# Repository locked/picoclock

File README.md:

# RP2040 based Alarm Clock

## Presentation

This repo is an attempt at building a Pico based alarm clock. It was created for my kids and features:

- date/time (obviously)
- alarm (plays wav file on sdcard)
- weather (current and forecast)
- epaper screen
- 3d printable case

The configuration is done remotely, and the clock synchronize from time to time (it can be forced too). The time is also fetched from a remote server.

## Repository Architecture

- **3d**: contains printable models for the case, buttons
- **fw**: the firmware, based on a lightweight "rtos"
- **pcb**: the PCBs:
  - the main PCB receiving the RP2040 board
  - the front PCB with the backlight leds
- **api**: remote api basic php script

## Pictures

## Build

```
mkdir build
cd build
cmake -DCMAKE_BUILD_TYPE=Debug ..
make
```

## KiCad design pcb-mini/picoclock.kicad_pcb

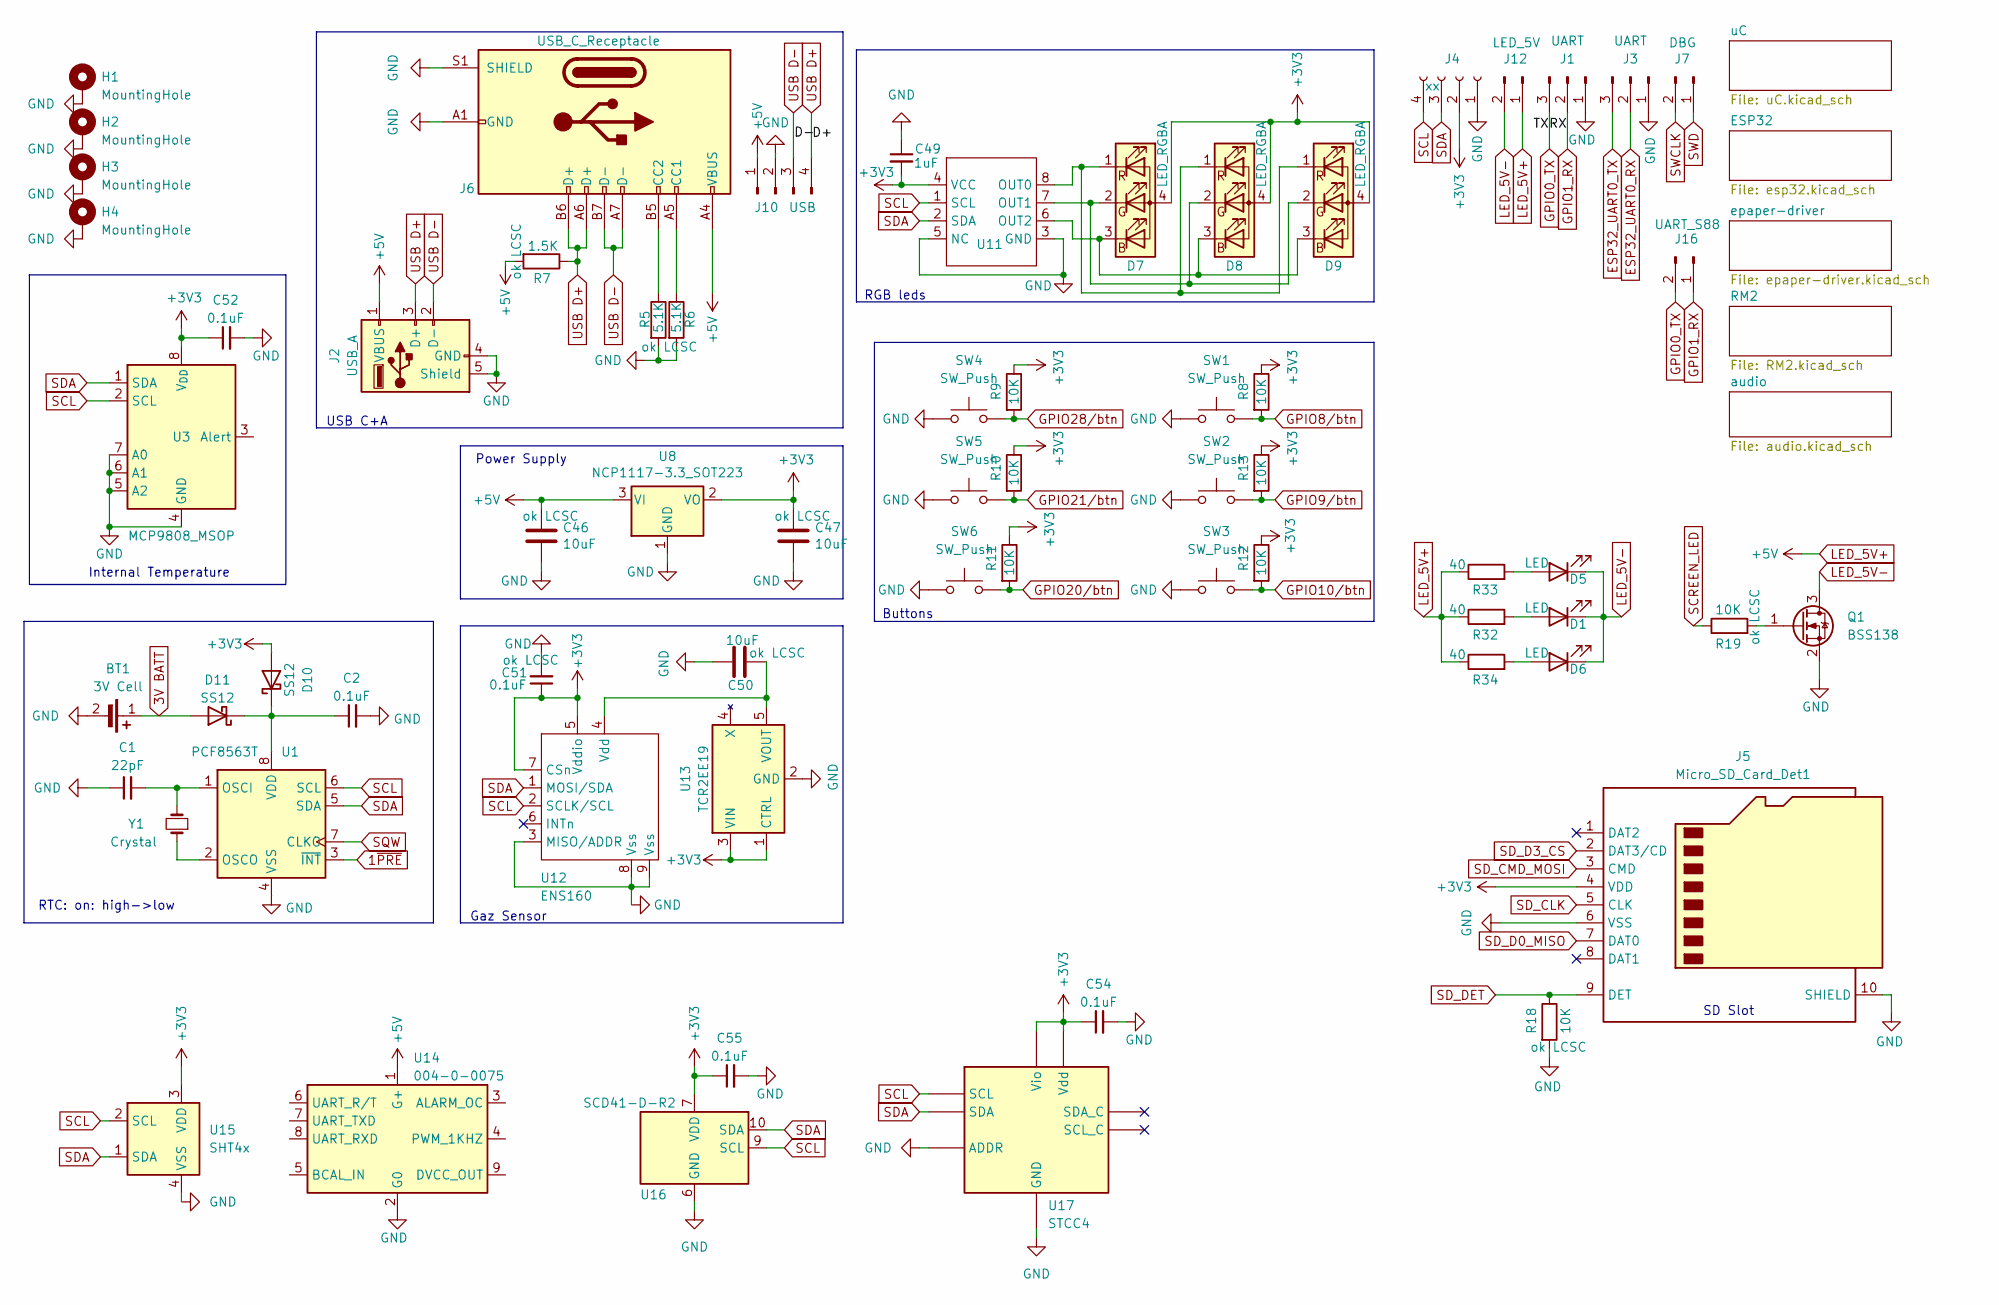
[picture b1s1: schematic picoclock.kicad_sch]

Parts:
BT1: 3V Cell; MPD_BC501SM-TR
C1: 22pF; C_0603_1608Metric; LCSC C1653
C2, C51, C52, C54, C55: 0.1uF; C_0603_1608Metric; LCSC C14663
C46, C47, C50: 10uF; C_0805_2012Metric; LCSC C15850
C49: 1uF; C_0603_1608Metric
D1, D5, D6: LED; LED_PLCC_2835
D7, D8, D9: LED_RGBA; LED_LiteOn_LTST-C19HE1WT
D10, D11: SS12; D_SOD-323
H1, H2, H3, H4: MountingHole; MountingHole_3.2mm_M3_Pad
J1, J3: UART; PinHeader_1x03_P2.54mm_Vertical
J2: USB_A; USB_A_Connfly_DS1095
J4: xx; PinSocket_1x04_P2.54mm_Vertical
J5: Micro_SD_Card_Det1; microSD_HC_Hirose_DM3AT-SF-PEJM5_combined_MSD-4-A
J6: USB_C_Receptacle; USB_C_Receptacle_GCT_USB4105-xx-A_16P_TopMnt_Horizontal
J7: DBG; PinHeader_1x02_P2.54mm_Vertical
J10: USB; PinHeader_1x04_P2.54mm_Vertical
J12: LED_5V; PinHeader_1x02_P2.54mm_Vertical
J16: UART_S88; PinHeader_1x02_P2.54mm_Vertical
Q1: BSS138; SOT-23-3
R5, R6: 5.1K; R_0603_1608Metric; LCSC C23186
R7: 1.5K; R_0603_1608Metric; LCSC C22843
R8, R9, R10, R11, R12, R13: 10K; R_0603_1608Metric; LCSC C25744
R18, R19: 10K; R_0402_1005Metric; LCSC C25744
R32, R33, R34: 40; R_0603_1608Metric
SW1, SW2, SW3, SW4, SW5, SW6: SW_Push; SW_SPST_TL3301TG
U1: PCF8563T; SOIC-8_3.9x4.9mm_P1.27mm; LCSC C7440
U3: MCP9808_MSOP; MSOP-8_3x3mm_P0.65mm; LCSC C129490
U8: NCP1117-3.3_SOT223; SOT-223-3_TabPin2
U11: LP5817
U12: ENS160
U13: TCR2EE19; SC-74A-5_1.55x2.9mm_P0.95mm
U14: 004-0-0075
U15: SHT4x; Sensirion_DFN-4_1.5x1.5mm_P0.8mm_SHT4x_NoCentralPad
U16: SCD41-D-R2; Sensirion_SCD4x-1EP_10.1x10.1mm_P1.25mm_EP4.8x4.8mm
U17: STCC4; LCSC C49191471
Y1: Crystal; Crystal_SMD_3215-2Pin_3.2x1.5mm; LCSC C32346

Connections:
1~PRE: U1.3 (~INT); also elsewhere on the board
3V BATT: BT1.1 (+), D11.2 (A)
+3V3: C47.1, C49.2, C51.1, C52.1, C54.1, C55.1, D7.4 (A), D8.4 (A), D9.4 (A), D10.2 (A), J4.2, J5.4 (VDD), R8.1, R9.1, R10.1, R11.1, R12.1, R13.1, U3.8 (V_{DD}), U8.2 (VO), U11.4 (VCC), U12.5 (Vddio), U12.7 (CSn), U13.1 (CTRL), U13.3 (VIN), U15.3 (VDD), U16.7 (VDD), U16.19 (VDD), U17.6 (Vio), U17.7 (Vdd); also elsewhere on the board
ESP32_UART0_RX: J3.2; also elsewhere on the board
ESP32_UART0_TX: J3.3; also elsewhere on the board
GND: BT1.2 (-), C1.1, C2.2, C46.2, C47.2, C49.1, C50.2, C51.2, C52.2, C54.2, C55.2, H1.1, H2.1, H3.1, H4.1, J1.1, J2.4 (GND), J2.5 (Shield), J3.1, J4.1, J5.6 (VSS), J5.10 (SHIELD), J6.A1 (GND), J6.A12 (GND), J6.B1 (GND), J6.B12 (GND), J6.S1 (SHIELD), J10.2, Q1.2 (S), R5.2, R6.2, R18.2, SW1.1, SW2.1, SW3.1, SW4.1, SW5.1, SW6.1, U1.4 (VSS), U3.4 (GND), U3.5 (A2), U3.6 (A1), U3.7 (A0), U8.1 (GND), U11.3 (GND), U11.5 (NC), U12.3 (MISO/ADDR), U12.8 (Vss), U12.9 (Vss), U13.2 (GND), U14.2 (G0), U15.4 (VSS), U16.6 (GND), U16.20 (GND), U16.21 (GND), U17.3 (ADDR), U17.4 (GND); also elsewhere on the board
GPIO0_TX: J1.3, J16.2; also elsewhere on the board
GPIO1_RX: J1.2, J16.1; also elsewhere on the board
GPIO8/btn: R8.2, SW1.2; also elsewhere on the board
GPIO9/btn: R13.2, SW2.2; also elsewhere on the board
GPIO10/btn: R12.2, SW3.2; also elsewhere on the board
GPIO20/btn: R11.2, SW6.2; also elsewhere on the board
GPIO21/btn: R10.2, SW5.2; also elsewhere on the board
GPIO28/btn: R9.2, SW4.2; also elsewhere on the board
LED_5V+: C46.1, J2.1 (VBUS), J6.A4 (VBUS), J6.A9 (VBUS), J6.B4 (VBUS), J6.B9 (VBUS), J10.1, J12.1, R7.2, R32.1, R33.1, R34.1, U8.3 (VI), U14.1 (G+)
LED_5V-: D1.1 (K), D5.1 (K), D6.1 (K), J12.2, Q1.3 (D)
unnamed: D1.2 (A), R32.2
unnamed: D5.2 (A), R33.2
unnamed: D6.2 (A), R34.2
unnamed: D7.3 (BK), D8.3 (BK), D9.3 (BK), U11.6 (OUT2)
unnamed: D7.2 (GK), D8.2 (GK), D9.2 (GK), U11.7 (OUT1)
unnamed: D7.1 (RK), D8.1 (RK), D9.1 (RK), U11.8 (OUT0)
unnamed: C2.1, D10.1 (K), D11.1 (K), U1.8 (VDD)
unnamed: J6.A5 (CC1), R6.1
unnamed: J6.B5 (CC2), R5.1
unnamed: Q1.1 (G), R19.2
unnamed: C1.2, U1.1 (OSCI), Y1.2
unnamed: U1.2 (OSCO), Y1.1
unnamed: C50.1, U12.4 (Vdd), U13.5 (VOUT)
SCL: J4.4, U1.6 (SCL), U3.2 (SCL), U11.1 (SCL), U12.2 (SCLK/SCL), U15.2 (SCL), U16.9 (SCL), U17.1 (SCL); also elsewhere on the board
SCREEN_LED: R19.1; also elsewhere on the board
SDA: J4.3, U1.5 (SDA), U3.1 (SDA), U11.2 (SDA), U12.1 (MOSI/SDA), U15.1 (SDA), U16.10 (SDA), U17.5 (SDA); also elsewhere on the board
SD_CLK: J5.5 (CLK); also elsewhere on the board
SD_CMD_MOSI: J5.3 (CMD); also elsewhere on the board
SD_D0_MISO: J5.7 (DAT0); also elsewhere on the board
SD_D3_CS: J5.2 (DAT3/CD); also elsewhere on the board
SD_DET: J5.9 (DET), R18.1; also elsewhere on the board
SQW: U1.7 (CLKO); also elsewhere on the board
SWCLK: J7.2; also elsewhere on the board
SWD: J7.1; also elsewhere on the board
USB D+: J2.3 (D+), J6.A6 (D+), J6.B6 (D+), J10.4, R7.1; also elsewhere on the board
USB D-: J2.2 (D-), J6.A7 (D-), J6.B7 (D-), J10.3; also elsewhere on the board

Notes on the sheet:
USB C+A
SD Slot
Internal Temperature
RTC: on: high->low
Power Supply
RGB leds
Buttons
Gaz Sensor

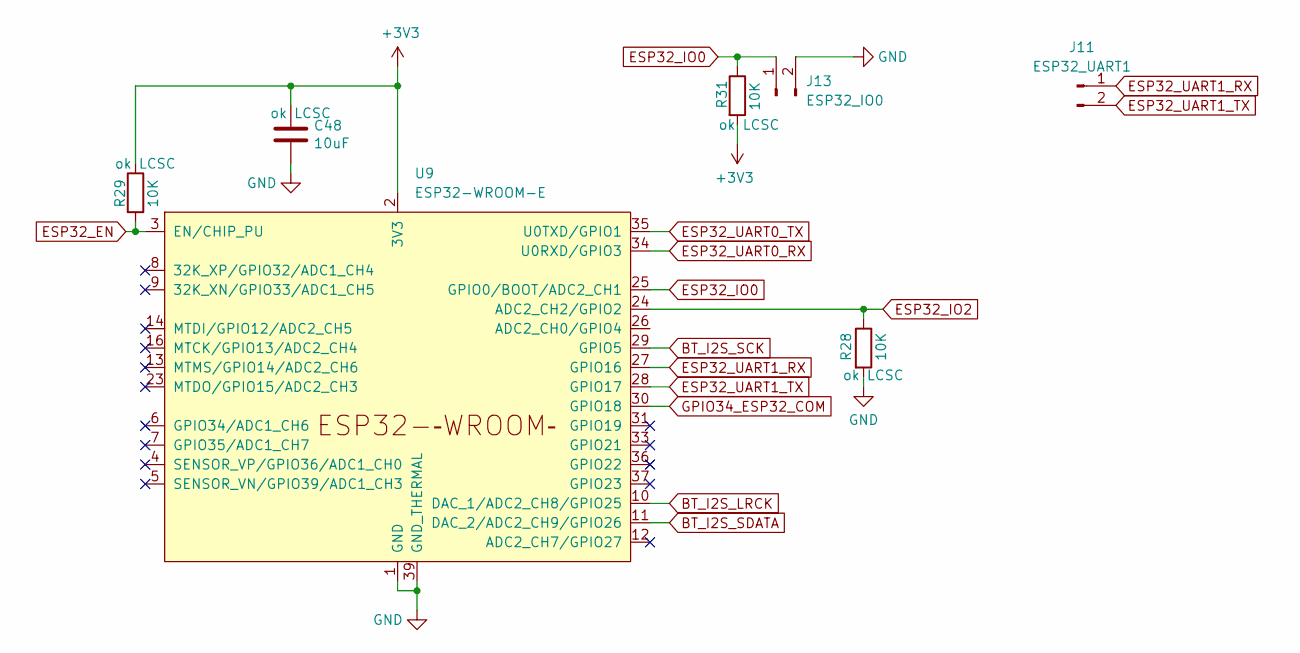
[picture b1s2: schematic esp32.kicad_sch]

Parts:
C48: 10uF; C_0805_2012Metric; LCSC C15850
J11: ESP32_UART1; PinHeader_1x02_P2.54mm_Vertical
J13: ESP32_IO0; PinHeader_1x02_P2.54mm_Vertical
R28, R29, R31: 10K; R_0402_1005Metric; LCSC C25744
U9: ESP32-WROOM-E; ESP32-WROOM-32E

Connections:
+3V3: C48.1, R29.1, R31.2, U9.2 (3V3); also elsewhere on the board
BT_I2S_LRCK: U9.10 (DAC_1/ADC2_CH8/GPIO25); also elsewhere on the board
BT_I2S_SCK: U9.29 (GPIO5); also elsewhere on the board
BT_I2S_SDATA: U9.11 (DAC_2/ADC2_CH9/GPIO26); also elsewhere on the board
ESP32_EN: R29.2, U9.3 (EN/CHIP_PU)
ESP32_IO0: J13.1, R31.1, U9.25 (GPIO0/BOOT/ADC2_CH1)
ESP32_IO2: R28.1, U9.24 (ADC2_CH2/GPIO2)
ESP32_UART0_RX: U9.34 (U0RXD/GPIO3); also elsewhere on the board
ESP32_UART0_TX: U9.35 (U0TXD/GPIO1); also elsewhere on the board
ESP32_UART1_RX: J11.1, U9.27 (GPIO16); also elsewhere on the board
ESP32_UART1_TX: J11.2, U9.28 (GPIO17); also elsewhere on the board
GND: C48.2, J13.2, R28.2, U9.1 (GND), U9.15 (GND), U9.38 (GND), U9.39 (GND_THERMAL); also elsewhere on the board
GPIO34_ESP32_COM: U9.30 (GPIO18); also elsewhere on the board

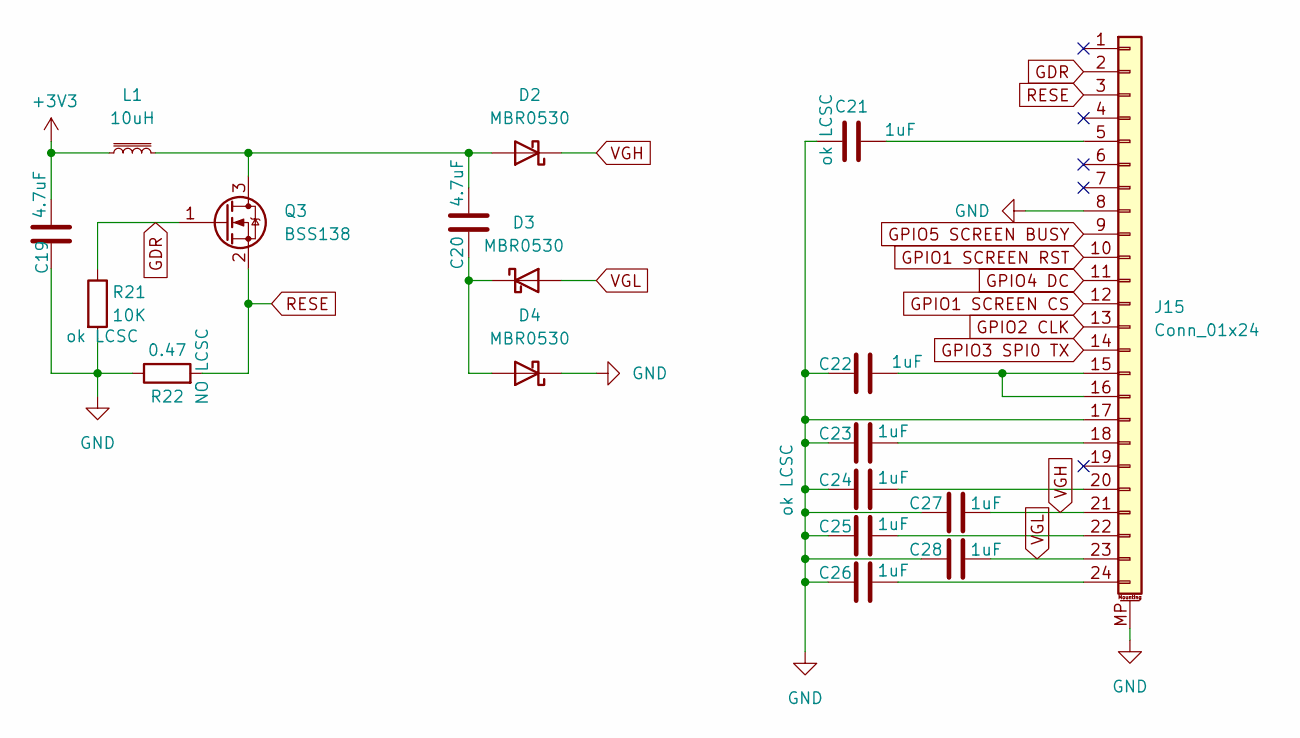
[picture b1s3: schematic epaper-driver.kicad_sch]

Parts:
C19, C20: 4.7uF; C_0603_1608Metric
C21, C22, C23, C24, C25, C26, C27, C28: 1uF; C_0603_1608Metric; LCSC C15849
D2, D3, D4: MBR0530; D_SOD-123
J15: Conn_01x24; Hirose_FH12-24S-0.5SH_1x24-1MP_P0.50mm_Horizontal
L1: 10uH; L_TDK_NLV32_3.2x2.5mm
Q3: BSS138; SOT-23-3
R21: 10K; R_0402_1005Metric; LCSC C25744
R22: 0.47; R_0603_1608Metric

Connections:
+3V3: C19.1, L1.1; also elsewhere on the board
GDR: J15.2, Q3.1 (G), R21.1
GND: C19.2, C21.2, C22.2, C23.2, C24.2, C25.2, C26.2, C27.2, C28.2, D4.1 (K), J15.8, J15.17, J15.MP (MountPin), R21.2, R22.1; also elsewhere on the board
GPIO1 SCREEN CS: J15.12; also elsewhere on the board
GPIO1 SCREEN RST: J15.10; also elsewhere on the board
GPIO2 CLK: J15.13; also elsewhere on the board
GPIO3 SPI0 TX: J15.14; also elsewhere on the board
GPIO4 DC: J15.11; also elsewhere on the board
GPIO5 SCREEN BUSY: J15.9; also elsewhere on the board
unnamed: C20.1, D2.2 (A), L1.2, Q3.3 (D)
unnamed: C20.2, D3.1 (K), D4.2 (A)
unnamed: C21.1, J15.5
unnamed: C22.1, J15.15, J15.16
unnamed: C23.1, J15.18
unnamed: C24.1, J15.20
unnamed: C25.1, J15.22
unnamed: C26.1, J15.24
RESE: J15.3, Q3.2 (S), R22.2
VGH: C27.1, D2.1 (K), J15.21
VGL: C28.1, D3.2 (A), J15.23

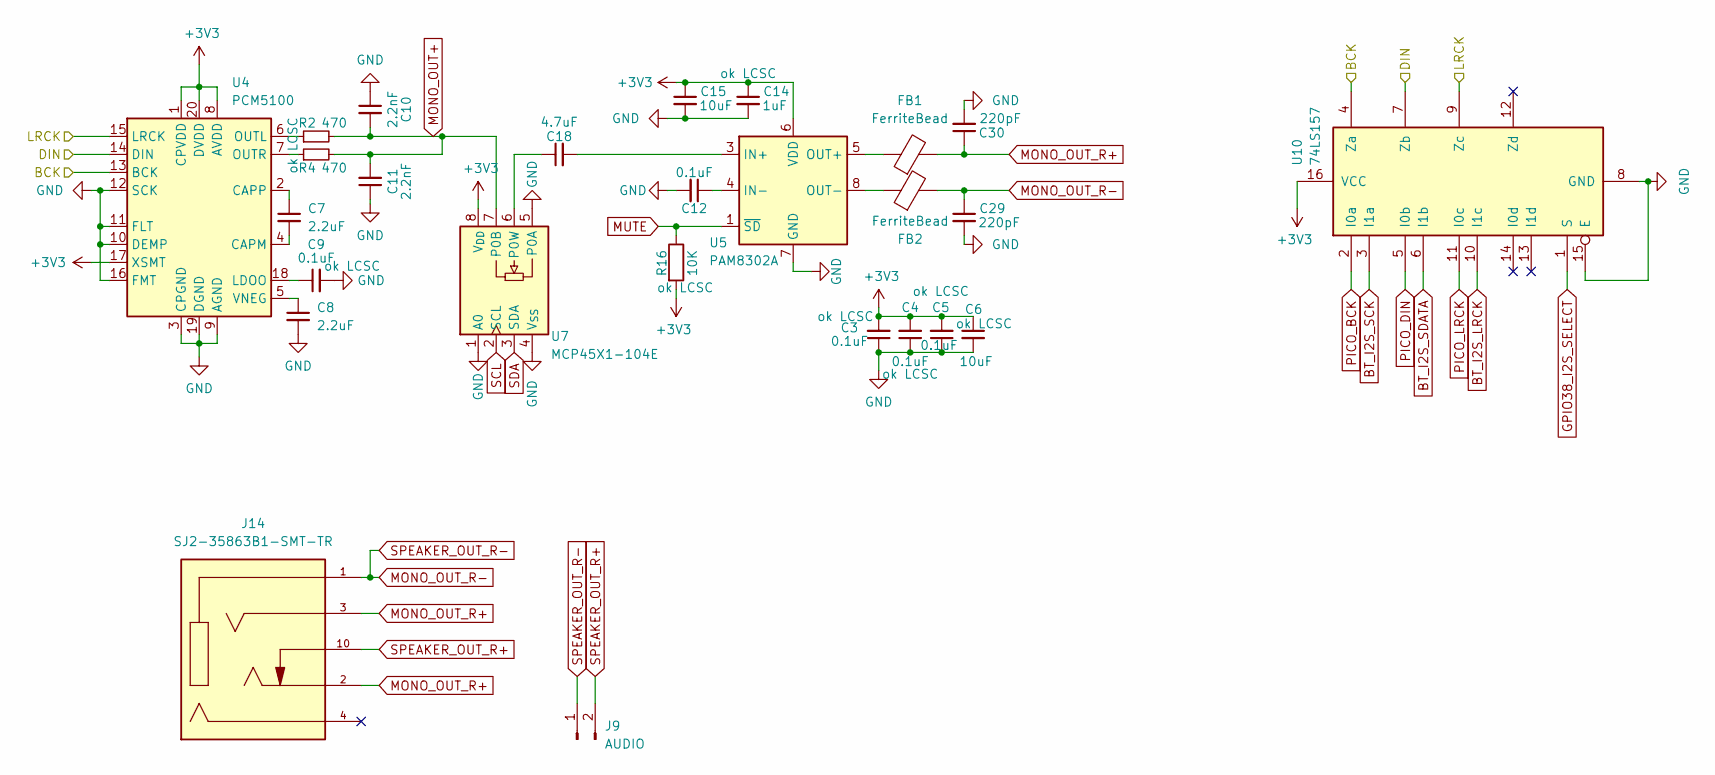
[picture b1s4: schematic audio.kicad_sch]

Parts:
C3, C4, C5, C9, C12: 0.1uF; C_0603_1608Metric; LCSC C14663
C6: 10uF; C_0805_2012Metric; LCSC C15850
C7: 2.2uF; C_0603_1608Metric
C8: 2.2uF; C_0402_1005Metric
C10, C11: 2.2nF; C_0603_1608Metric
C14: 1uF; C_0603_1608Metric; LCSC C15849
C15: 10uF; C_0603_1608Metric
C18: 4.7uF; C_0603_1608Metric
C29, C30: 220pF; C_0603_1608Metric
FB1, FB2: FerriteBead; L_0603_1608Metric
J9: AUDIO; PinHeader_1x02_P2.54mm_Vertical
J14: SJ2-35863B1-SMT-TR; CUI_SJ2-35863B1-SMT-TR; PARTREV 1.04
R2, R4: 470; R_0603_1608Metric; LCSC C23179
R16: 10K; R_0402_1005Metric; LCSC C25744
U4: PCM5100; TSSOP-20_4.4x6.5mm_P0.65mm
U5: PAM8302A; SOP-8_3.76x4.96mm_P1.27mm
U7: MCP45X1-104E; MSOP-8_3x3mm_P0.65mm
U10: 74LS157; SOP-16_4.55x10.3mm_P1.27mm

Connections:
+3V3: C3.2, C4.2, C5.2, C6.1, C14.1, C15.1, R16.2, U4.1 (CPVDD), U4.8 (AVDD), U4.17 (XSMT), U4.20 (DVDD), U5.6 (VDD), U7.8 (V_{DD}), U10.16 (VCC); also elsewhere on the board
/audio/BCK: U4.13 (BCK), U10.4 (Za)
/audio/DIN: U4.14 (DIN), U10.7 (Zb)
/audio/LRCK: U4.15 (LRCK), U10.9 (Zc)
BT_I2S_LRCK: U10.10 (I1c); also elsewhere on the board
BT_I2S_SCK: U10.3 (I1a); also elsewhere on the board
BT_I2S_SDATA: U10.6 (I1b); also elsewhere on the board
GND: C3.1, C4.1, C5.1, C6.2, C8.2, C9.2, C10.1, C11.1, C12.2, C14.2, C15.2, C29.2, C30.2, U4.3 (CPGND), U4.9 (AGND), U4.10 (DEMP), U4.11 (FLT), U4.12 (SCK), U4.16 (FMT), U4.19 (DGND), U5.7 (GND), U7.1 (A0), U7.4 (V_{SS}), U7.5 (P0A), U10.8 (GND), U10.15 (E); also elsewhere on the board
GPIO38_I2S_SELECT: U10.1 (S); also elsewhere on the board
MONO_OUT+: C10.2, C11.2, R2.2, R4.2, U7.7 (P0B)
MONO_OUT_R+: C30.1, FB1.2, J14.2, J14.3
MONO_OUT_R-: C29.1, FB2.2, J9.1, J14.1
MUTE: R16.1, U5.1 (~SD); also elsewhere on the board
unnamed: C7.2, U4.4 (CAPM)
unnamed: C7.1, U4.2 (CAPP)
unnamed: C9.1, U4.18 (LDOO)
unnamed: R2.1, U4.6 (OUTL)
unnamed: R4.1, U4.7 (OUTR)
unnamed: C8.1, U4.5 (VNEG)
unnamed: C18.2, U5.3 (IN+)
unnamed: C12.1, U5.4 (IN-)
unnamed: FB1.1, U5.5 (OUT+)
unnamed: FB2.1, U5.8 (OUT-)
unnamed: C18.1, U7.6 (P0W)
PICO_BCK: U10.2 (I0a); also elsewhere on the board
PICO_DIN: U10.5 (I0b); also elsewhere on the board
PICO_LRCK: U10.11 (I0c); also elsewhere on the board
SCL: U7.2 (SCL); also elsewhere on the board
SDA: U7.3 (SDA); also elsewhere on the board
SPEAKER_OUT_R+: J9.2, J14.10

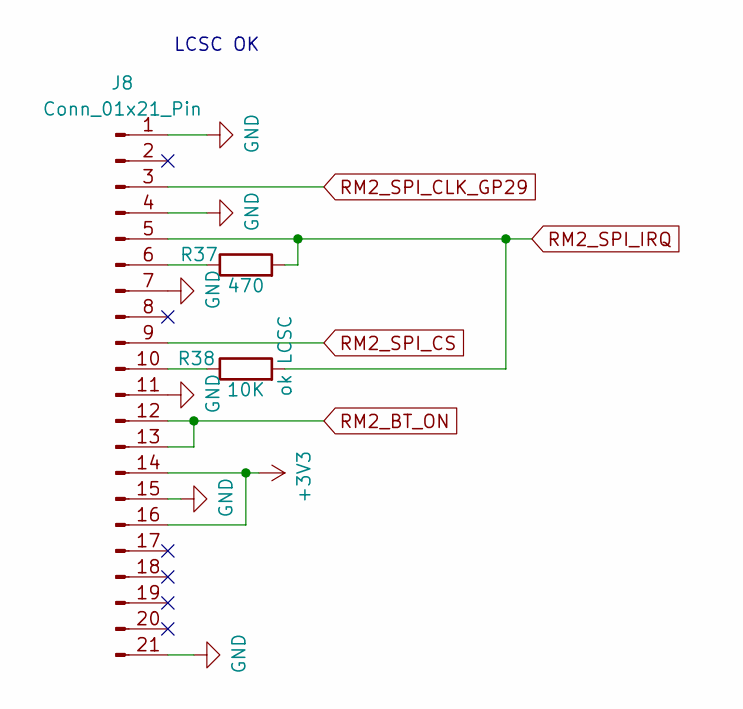
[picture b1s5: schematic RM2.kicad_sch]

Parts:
J8: Conn_01x21_Pin; RMC20452T
R37: 470; R_0603_1608Metric; LCSC C23179
R38: 10K; R_0402_1005Metric; LCSC C25744

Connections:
+3V3: J8.14, J8.16; also elsewhere on the board
GND: J8.1, J8.4, J8.7, J8.11, J8.15, J8.21; also elsewhere on the board
unnamed: J8.6, R37.1
unnamed: J8.10, R38.1
RM2_BT_ON: J8.12, J8.13; also elsewhere on the board
RM2_SPI_CLK_GP29: J8.3; also elsewhere on the board
RM2_SPI_CS: J8.9; also elsewhere on the board
RM2_SPI_IRQ: J8.5, R37.2, R38.2; also elsewhere on the board

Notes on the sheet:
LCSC OK

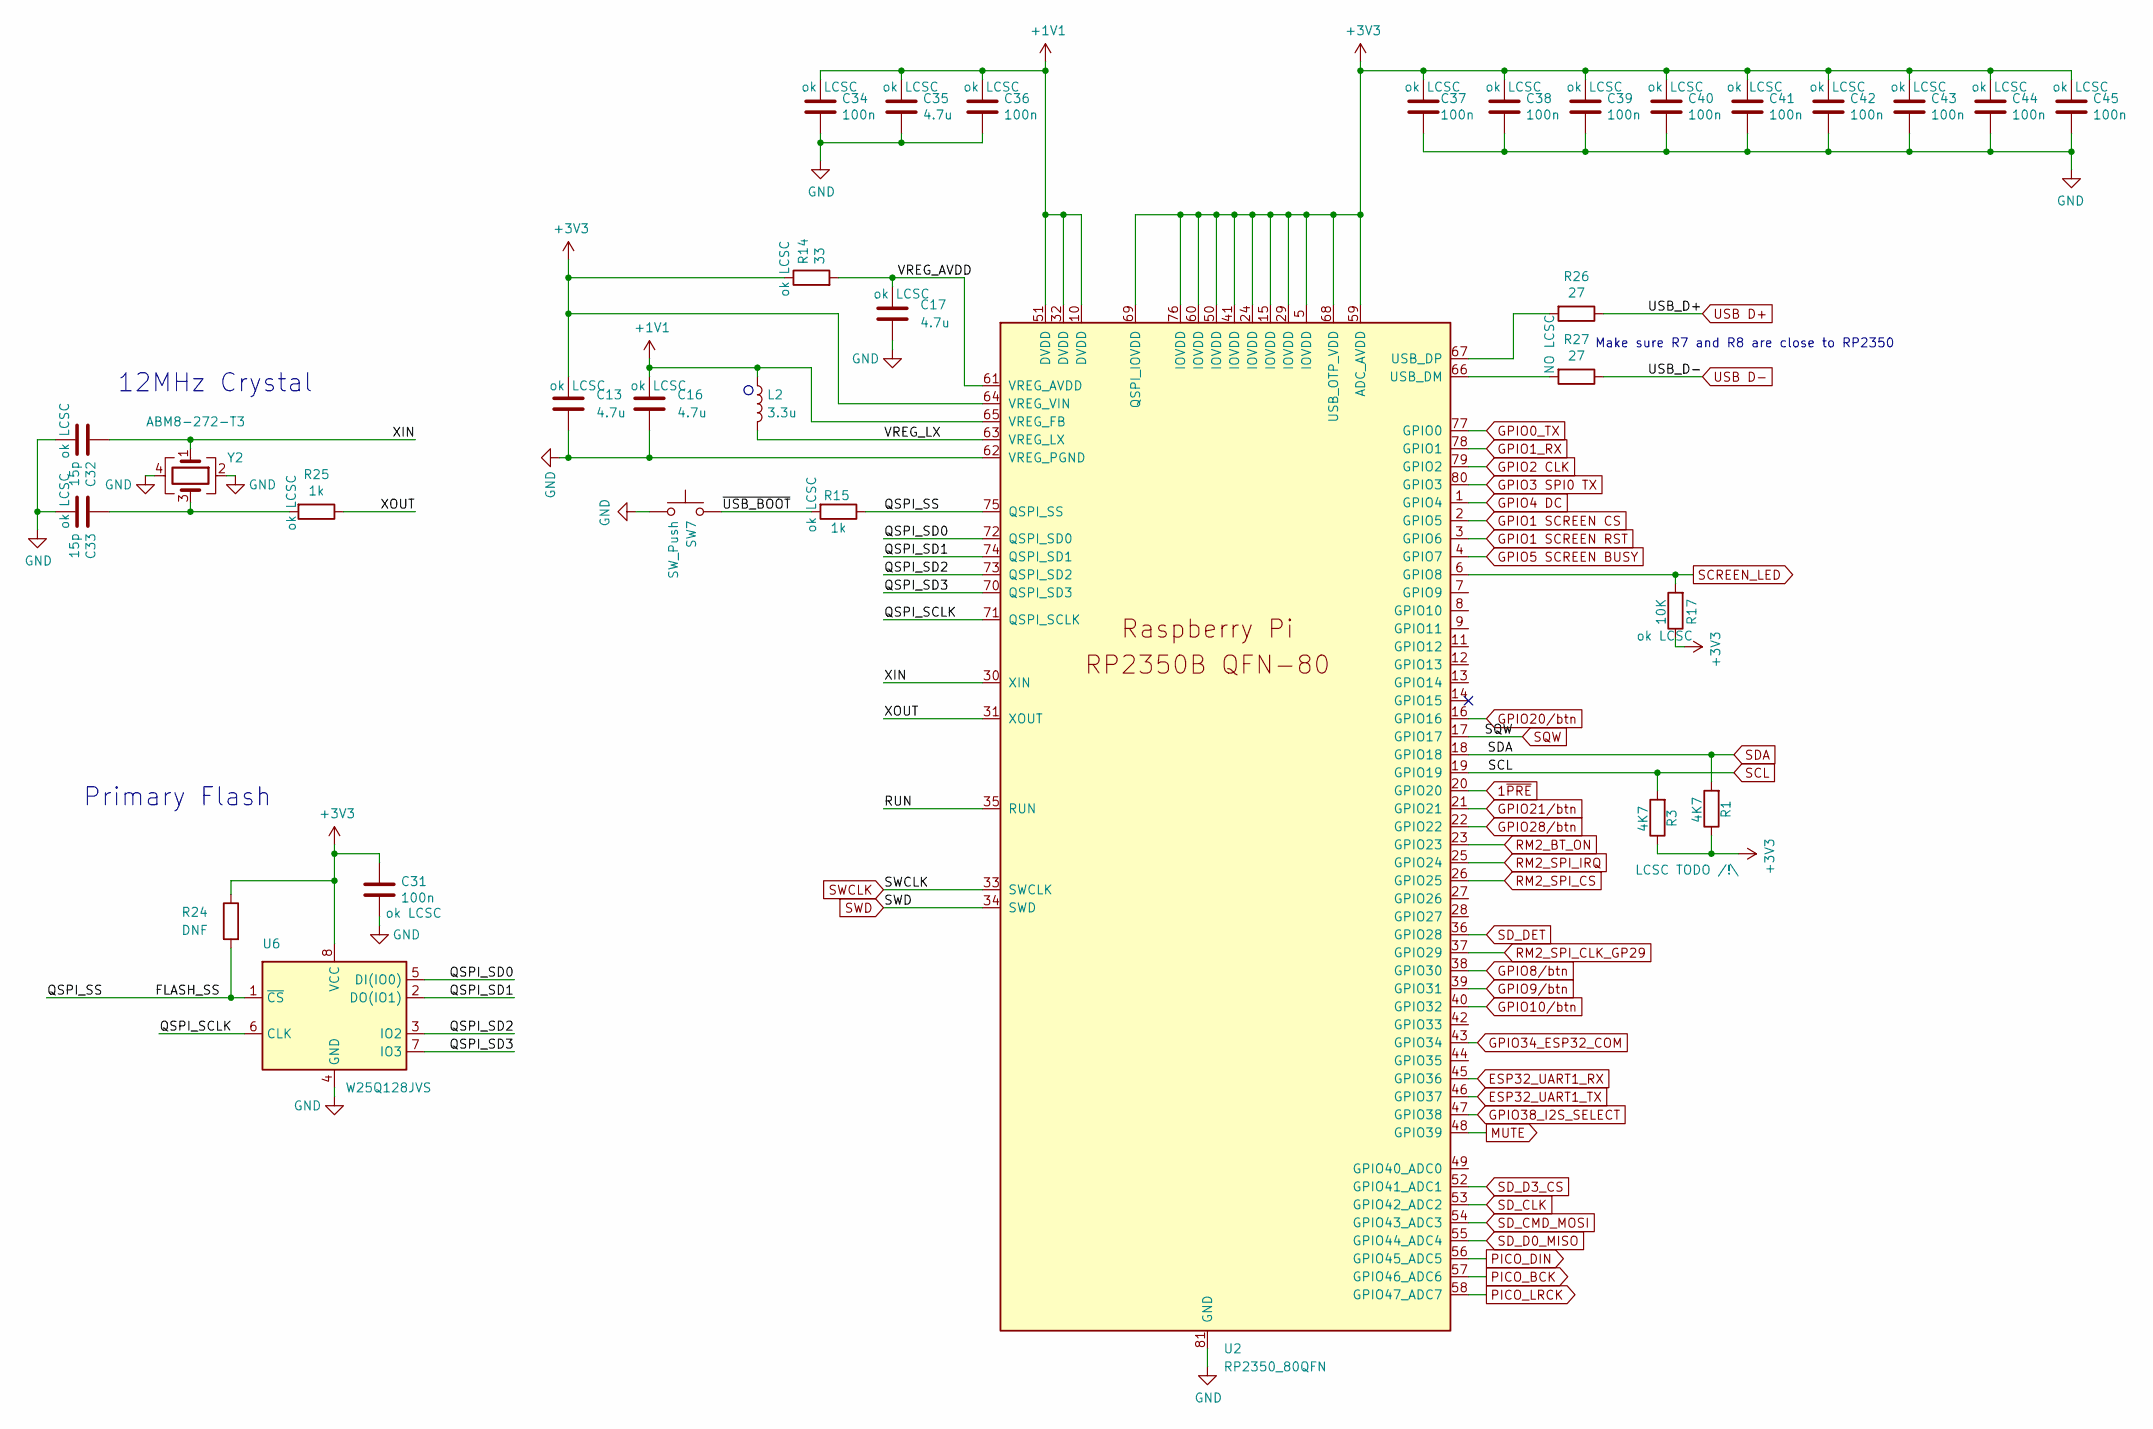
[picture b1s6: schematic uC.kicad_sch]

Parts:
C13, C16: 4.7u; C_0402_1005Metric_small_pads; LCSC C23733
C17, C35: 4.7u; C_0402_1005Metric; LCSC C23733
C31, C34, C36, C37, C38, C39, C40, C41, C42, C43, C44, C45: 100n; C_0402_1005Metric; LCSC C1525
C32, C33: 15p; C_0402_1005Metric; LCSC C1548
L2: 3.3u; L_pol_2016; LCSC C42411119
R1, R3: 4K7; R_0402_1005Metric
R14: 33; R_0402_1005Metric; LCSC C25105
R15, R25: 1k; R_0402_1005Metric; LCSC C11702
R17: 10K; R_0402_1005Metric; LCSC C25744
R24: DNF; R_0402_1005Metric
R26, R27: 27; R_0402_1005Metric
SW7: SW_Push; SW_Tactile_SPST_Angled_PTS645Vx31-2LFS
U2: RP2350_80QFN; RP2350-QFN-80-1EP_10x10_P0.4mm_EP3.4x3.4mm_ThermalVias; LCSC C39843328
U6: W25Q128JVS; SOIC-8_5.3x5.3mm_P1.27mm
Y2: ABM8-272-T3; Crystal_SMD_3225-4Pin_3.2x2.5mm

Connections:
1~PRE: U2.20 (GPIO20); also elsewhere on the board
+1V1: C16.1, C34.1, C35.1, C36.1, L2.1, U2.10 (DVDD), U2.32 (DVDD), U2.51 (DVDD), U2.65 (VREG_FB)
+3V3: C13.1, C31.1, C37.1, C38.1, C39.1, C40.1, C41.1, C42.1, C43.1, C44.1, C45.1, R1.1, R3.1, R14.1, R17.1, R24.1, U2.5 (IOVDD), U2.15 (IOVDD), U2.24 (IOVDD), U2.29 (IOVDD), U2.41 (IOVDD), U2.50 (IOVDD), U2.59 (ADC_AVDD), U2.60 (IOVDD), U2.64 (VREG_VIN), U2.68 (USB_OTP_VDD), U2.69 (QSPI_IOVDD), U2.76 (IOVDD), U6.8 (VCC); also elsewhere on the board
/uC/FLASH_SS: R15.1, R24.2, U2.75 (QSPI_SS), U6.1 (~CS)
/uC/QSPI_SCLK: U2.71 (QSPI_SCLK), U6.6 (CLK)
/uC/QSPI_SD0: U2.72 (QSPI_SD0), U6.5 (DI(IO0))
/uC/QSPI_SD1: U2.74 (QSPI_SD1), U6.2 (DO(IO1))
/uC/QSPI_SD2: U2.73 (QSPI_SD2), U6.3 (IO2)
/uC/QSPI_SD3: U2.70 (QSPI_SD3), U6.7 (IO3)
/uC/RUN: U2.35 (RUN)
/uC/VREG_AVDD: C17.1, R14.2, U2.61 (VREG_AVDD)
/uC/VREG_LX: L2.2, U2.63 (VREG_LX)
/uC/XIN: C32.1, U2.30 (XIN), Y2.1
/uC/XOUT: R25.1, U2.31 (XOUT)
/uC/~USB_BOOT: R15.2, SW7.2
ESP32_UART1_RX: U2.45 (GPIO36); also elsewhere on the board
ESP32_UART1_TX: U2.46 (GPIO37); also elsewhere on the board
GND: C13.2, C16.2, C17.2, C31.2, C32.2, C33.2, C34.2, C35.2, C36.2, C37.2, C38.2, C39.2, C40.2, C41.2, C42.2, C43.2, C44.2, C45.2, SW7.1, U2.62 (VREG_PGND), U2.81 (GND), U6.4 (GND), Y2.2, Y2.4; also elsewhere on the board
GPIO0_TX: U2.77 (GPIO0); also elsewhere on the board
GPIO1 SCREEN CS: U2.2 (GPIO5); also elsewhere on the board
GPIO1 SCREEN RST: U2.3 (GPIO6); also elsewhere on the board
GPIO1_RX: U2.78 (GPIO1); also elsewhere on the board
GPIO2 CLK: U2.79 (GPIO2); also elsewhere on the board
GPIO3 SPI0 TX: U2.80 (GPIO3); also elsewhere on the board
GPIO4 DC: U2.1 (GPIO4); also elsewhere on the board
GPIO5 SCREEN BUSY: U2.4 (GPIO7); also elsewhere on the board
GPIO8/btn: U2.38 (GPIO30); also elsewhere on the board
GPIO9/btn: U2.39 (GPIO31); also elsewhere on the board
GPIO10/btn: U2.40 (GPIO32); also elsewhere on the board
GPIO20/btn: U2.16 (GPIO16); also elsewhere on the board
GPIO21/btn: U2.21 (GPIO21); also elsewhere on the board
GPIO28/btn: U2.22 (GPIO22); also elsewhere on the board
GPIO34_ESP32_COM: U2.43 (GPIO34); also elsewhere on the board
GPIO38_I2S_SELECT: U2.47 (GPIO38); also elsewhere on the board
MUTE: U2.48 (GPIO39); also elsewhere on the board
unnamed: C33.1, R25.2, Y2.3
unnamed: R27.2, U2.66 (USB_DM)
unnamed: R26.2, U2.67 (USB_DP)
PICO_BCK: U2.57 (GPIO46_ADC6); also elsewhere on the board
PICO_DIN: U2.56 (GPIO45_ADC5); also elsewhere on the board
PICO_LRCK: U2.58 (GPIO47_ADC7); also elsewhere on the board
RM2_BT_ON: U2.23 (GPIO23); also elsewhere on the board
RM2_SPI_CLK_GP29: U2.37 (GPIO29); also elsewhere on the board
RM2_SPI_CS: U2.26 (GPIO25); also elsewhere on the board
RM2_SPI_IRQ: U2.25 (GPIO24); also elsewhere on the board
SCL: R3.2, U2.19 (GPIO19); also elsewhere on the board
SCREEN_LED: R17.2, U2.6 (GPIO8); also elsewhere on the board
SDA: R1.2, U2.18 (GPIO18); also elsewhere on the board
SD_CLK: U2.53 (GPIO42_ADC2); also elsewhere on the board
SD_CMD_MOSI: U2.54 (GPIO43_ADC3); also elsewhere on the board
SD_D0_MISO: U2.55 (GPIO44_ADC4); also elsewhere on the board
SD_D3_CS: U2.52 (GPIO41_ADC1); also elsewhere on the board
SD_DET: U2.36 (GPIO28); also elsewhere on the board
SQW: U2.17 (GPIO17); also elsewhere on the board
SWCLK: U2.33 (SWCLK); also elsewhere on the board
SWD: U2.34 (SWD); also elsewhere on the board
USB D+: R26.1; also elsewhere on the board
USB D-: R27.1; also elsewhere on the board

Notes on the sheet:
Make sure R7 and R8 are close to RP2350
12MHz Crystal
Primary Flash

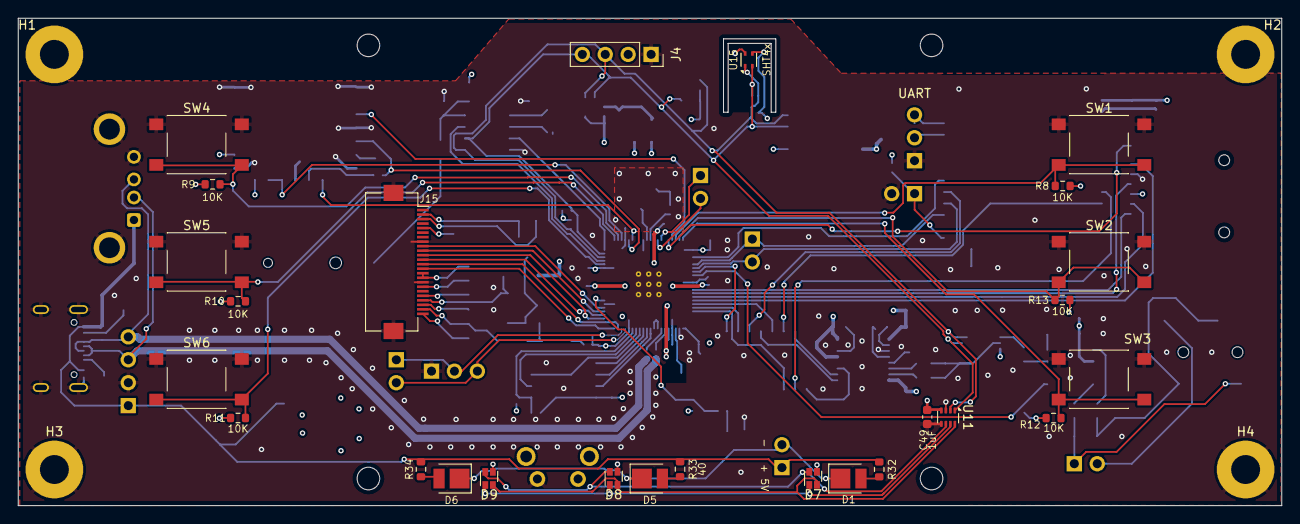
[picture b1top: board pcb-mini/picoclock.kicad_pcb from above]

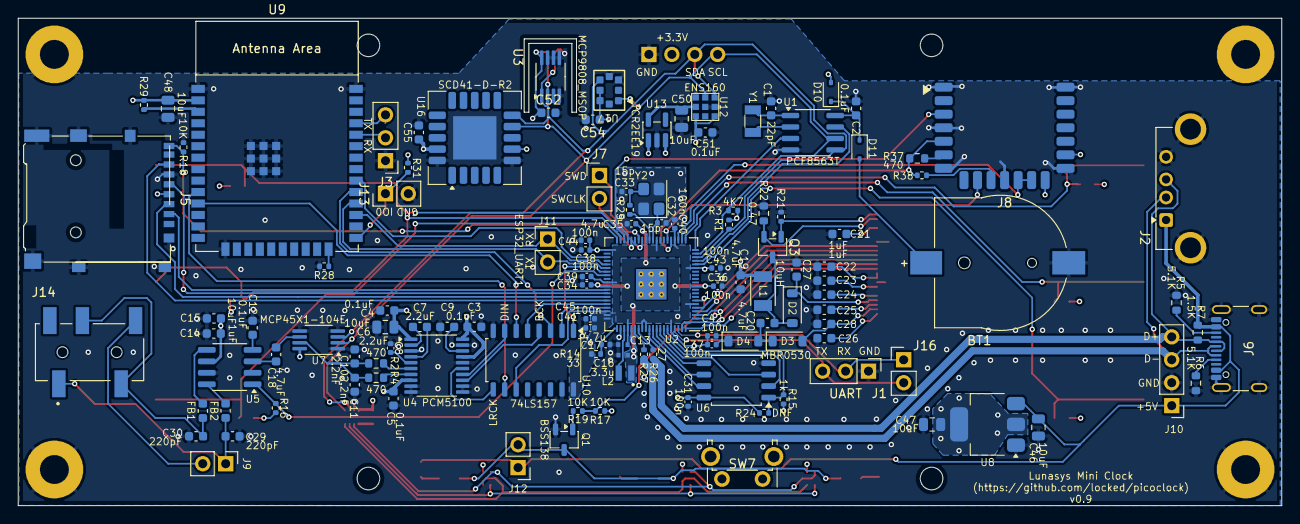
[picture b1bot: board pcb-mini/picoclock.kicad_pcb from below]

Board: 4 copper layers, 140.0 x 54.0 mm, 150 parts (120 on the bottom side), 113 nets.

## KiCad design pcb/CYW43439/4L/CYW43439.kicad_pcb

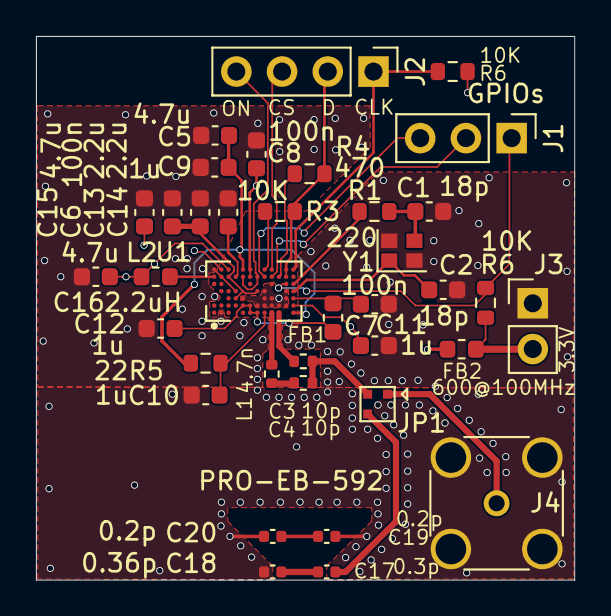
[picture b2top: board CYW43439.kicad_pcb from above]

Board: 4 copper layers, 29.9 x 30.2 mm, 37 parts (0 on the bottom side), 31 nets.

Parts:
C1, C2: 18p; C_0603_1608Metric
C3, C4: 10p; R_0402_1005Metric
C5, C15, C16: 4.7u; C_0603_1608Metric
C6, C8, C11: 100n; C_0603_1608Metric
C7, C9, C10, C12: 1u; C_0603_1608Metric
C13, C14: 2.2u; C_0603_1608Metric
C17: 0.3p; C_0402_1005Metric
C18: 0.36p; C_0402_1005Metric
C19, C20: 0.2p; C_0402_1005Metric
FB1, FB2: 600@100MHz; L_0603_1608Metric
J1: GPIOs; PinHeader_1x03_P2.54mm_Vertical
J2: SPI; PinHeader_1x04_P2.54mm_Vertical
J3: Power; PinHeader_1x02_P2.54mm_Vertical
J4: RP-SMA Female; SMA_Amphenol_132134-14_Vertical
JP1: SolderJumper_3_Open; SolderJumper-3_P1.3mm_Open_Pad1.0x1.5mm
L1: 4.7n; R_0402_1005Metric
L2: 2.2uH; L_0603_1608Metric
R1: 220; R_0603_1608Metric
R3, R6, R6#2: 10K; R_0603_1608Metric
R4: 470; R_0603_1608Metric
R5: 22; R_0603_1608Metric
U1: CYW43439KUBGT; BGA63N40P7X12_287X487X55N
Y1: Crystal; Crystal_SMD_2016-4Pin_2.0x1.6mm

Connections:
+3.3V: FB2.2, J3.2, R6.2
ANTENNA: C17.1, JP1.3 (B)
BT_PAVDD: C10.1, R5.2, U1.H1 (BT_PAVDD)
GND: C1.2, C2.2, C5.2, C6.2, C7.2, C8.2, C9.2, C10.2, C11.2, C12.2, C13.2, C14.2, C15.2, C16.2, C18.2, C19.1, C20.2, J3.1, J4.2 (Ext), R6#2.2, U1.A7 (SR_PVSS), U1.B1 (BT_DEV_WAKE), U1.B6 (PMU_AVSS), U1.D4 (VSSC), U1.E3 (FM_RF_VSS), U1.G2 (BTFM_PLL_VSS), U1.H2 (BT_IF_VSS), U1.H3 (BT_VCO_VSS), U1.H4 (WLRF_AFE_GND), U1.J2 (WLRF_LNA_GND), U1.J3 (WLRF_GPIO), U1.J5 (VSSC), U1.K2 (WLRF_GENERAL_GND), U1.L2 (WLRF_PA_GND), U1.L3 (WLRF_VCO_GND), U1.L4 (WLRF_XTAL_GND), Y1.2, Y1.4
unnamed: C1.1, R1.2, Y1.3
unnamed: C4.1, L1.2
unnamed: C17.2, C18.1
unnamed: C19.2, C20.1
unnamed: J4.1 (In), JP1.1 (A)
unnamed: C3.2, C4.2, JP1.2 (C)
unnamed: C12.1, FB1.1, U1.E2 (FM_RF_VDD), U1.F1 (BT_VCO_VDD), U1.F2 (BTFM_PLL_VDD), U1.G1 (BT_IF_VDD)
unnamed: R4.1, U1.K6 (SDIO_DATA_0)
unnamed: R3.1, U1.H7 (SDIO_DATA_1)
unnamed: C3.1, U1.K1 (WLRF_2G_RF)
unnamed: R1.1, U1.M5 (WLRF_XTAL_XON)
unnamed: C2.1, U1.M4 (WLRF_XTAL_XOP), Y1.1
SR_VLX: L2.2, U1.A6 (SR_VLX)
VDDBAT: C8.1, C15.1, FB2.1, U1.B7 (SR_VDDBAT5V), U1.F6 (WCC_VDDIO), U1.F7 (LDO_VDDBAT5V)
VIN_LDO: C7.1, C16.1, L2.1, U1.C7 (LDO_VDD1P5), U1.M2 (WLRF_VDD_1P35)
VOUT_3P3: C5.1, C9.1, R5.1, U1.E7 (VOUT_3P3), U1.M1 (WLRF_PA_VDD)
VOUT_CORE: C6.1, C13.1, U1.C6 (VOUT_CLDO), U1.D3 (VDDC), U1.G4 (VDDC)
VOUT_LN: C14.1, U1.D6 (VOUT_LNLDO)
WLRF_2G_ELG: L1.1, U1.J1 (WLRF_2G_ELG)
WL_CLK: J2.1, R6#2.1, U1.M7 (SDIO_CLK)
WL_CS: J2.3, U1.J7 (SDIO_DATA_3)
WL_D: J2.2, R3.2, R4.2, U1.L6 (SDIO_CMD), U1.L7 (SDIO_DATA_2)
WL_GPIO0: J1.2, U1.J6 (GPIO_0)
WL_GPIO1: J1.3, U1.H6 (GPIO_1)
WL_GPIO2: J1.1, R6.1, U1.L5 (GPIO_2)
WL_ON: J2.4, U1.E6 (BT_REG_ON), U1.G6 (WL_REG_ON)
XTAL_VDD: C11.1, FB1.2, U1.M3 (WLRF_XTAL_VDD1P2)

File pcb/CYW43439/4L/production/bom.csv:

Designator,Footprint,Quantity,Value,LCSC Part #
"C1, C2",0603,2,18p,C1647
"C10, C12, C7, C9",0603,4,1u,C15849
"C11, C6, C8",0603,3,100n,C14663
"C13, C14",0603,2,2.2u,C23630
"C15, C16, C5",0603,3,4.7u,C19666
C17,0402,1,0.3p,C880415
C18,0402,1,0.36p,
"C19, C20",0402,2,0.2p,C2836760
"C3, C4",0402,2,10p,C32949
"FB1, FB2",0603,2,600@100MHz,
J1,PinHeader_1x03_P2.54mm_Vertical,1,GPIOs,
J2,PinHeader_1x04_P2.54mm_Vertical,1,SPI,
J3,PinHeader_1x02_P2.54mm_Vertical,1,Power,
J4,SMA_Amphenol_132134-14_Vertical,1,RP-SMA Female,
L1,0402,1,4.7n,
L2,0603,1,2.2uH,
R1,0603,1,220,C22962
"R3, R6",0603,2,10K,C25804
R4,0603,1,470, C23179
R5,0603,1,22,C23345
U1,BGA63N40P7X12_287X487X55N,1,CYW43439KUBGT,C5359496
Y1,Crystal_SMD_2016-4Pin_2.0x1.6mm,1,Crystal,C2901740
